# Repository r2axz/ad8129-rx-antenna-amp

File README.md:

# AD8129 RX Antenna Amp

This repository offers a KiCad project for DL2KQ high CMRR receiving antenna
amplifier. The amplifier is designed to work with magnetic loop, flag, ferrite
rod, and similar antennas. IIgor DL2KQ Goncharenko developed the original
circuit, which I left pretty much unchanged, except I added a couple of extra
capacitors for power supply and varactor bias decoupling. Refer to the original
post (in Russian) [http://dl2kq.de/ant/3-96.htm](http://dl2kq.de/ant/3-96.htm)
or [autogenerated English
translation](https://translate.google.com/translate?js=n&sl=auto&tl=en&u=http://dl2kq.de/ant/3-96.htm).

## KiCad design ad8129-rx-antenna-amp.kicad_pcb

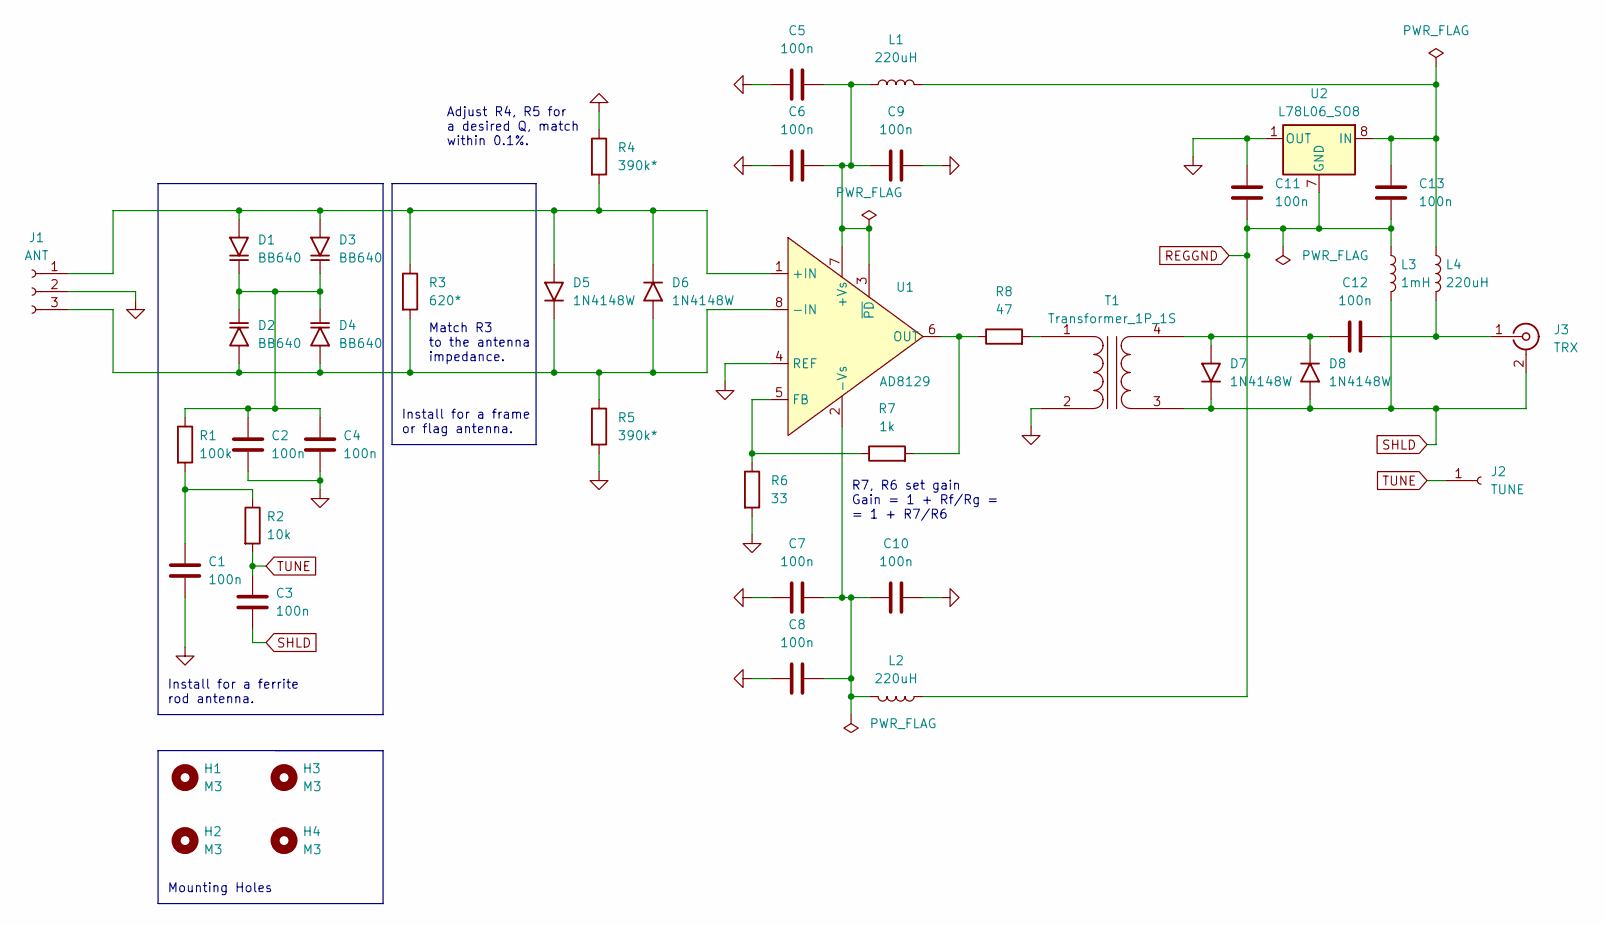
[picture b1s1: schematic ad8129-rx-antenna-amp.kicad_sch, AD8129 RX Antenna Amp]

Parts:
C1, C2, C3, C4, C5, C6, C7, C8, C9, C10, C11, C12, C13: 100n; C_0805_2012Metric
D1, D2, D3, D4: BB640; D_SOD-323
D5, D6, D7, D8: 1N4148W; D_SOD-123
H1, H2, H3, H4: M3; MountingHole_3.2mm_M3
J1: ANT; WirePad_3_0.8_1.5
J2: TUNE; WirePad_1_0.8_1.5
J3: TRX; SMA_Samtec_SMA-J-P-X-ST-EM1_EdgeMount
L1, L2, L4: 220uH; L_1812_4532Metric_Pad1.30x3.40mm_HandSolder
L3: 1mH; L_1812_4532Metric_Pad1.30x3.40mm_HandSolder
R1: 100k; R_0805_2012Metric
R2: 10k; R_0805_2012Metric
R3: 620*; R_0805_2012Metric
R4, R5: 390k*; R_0805_2012Metric
R6: 33; R_0805_2012Metric
R7: 1k; R_0805_2012Metric
R8: 47; R_0805_2012Metric
T1: Transformer_1P_1S; TR-FT-50-43-1P-1S-Isolated
U1: AD8129; SOIC-8_3.9x4.9mm_P1.27mm
U2: L78L06_SO8; SOIC-8_3.9x4.9mm_P1.27mm

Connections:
GND: C1.2, C2.2, C4.2, C5.1, C6.1, C7.2, C8.2, C9.2, C10.1, C11.1, J1.2, R4.1, R5.2, R6.2, T1.2 (AB), U1.4 (REF), U2.1 (OUT)
unnamed: C1.1, R1.2, R2.1
unnamed: C2.1, C4.1, D1.1 (K), D2.1 (K), D3.1 (K), D4.1 (K), R1.1
unnamed: C5.2, C6.2, C9.1, L1.1, U1.3 (~PD), U1.7 (+Vs)
unnamed: C7.1, C8.1, C10.2, L2.2, U1.2 (-Vs)
unnamed: C12.1, D7.2 (A), D8.1 (K), T1.4 (SB)
unnamed: C12.2, J3.1 (In), L4.2
unnamed: C13.1, L1.2, L4.1, U2.8 (IN)
unnamed: D1.2 (A), D3.2 (A), D5.2 (A), D6.1 (K), J1.1, R3.1, R4.2, U1.1 (+IN)
unnamed: D2.2 (A), D4.2 (A), D5.1 (K), D6.2 (A), J1.3, R3.2, R5.1, U1.8 (-IN)
unnamed: R6.1, R7.1, U1.5 (FB)
unnamed: R7.2, R8.1, U1.6 (OUT)
unnamed: R8.2, T1.1 (AA)
REGGND: C11.2, C13.2, L2.1, L3.1, U2.2 (GND), U2.3 (GND), U2.6 (GND), U2.7 (GND)
SHLD: C3.2, D7.1 (K), D8.2 (A), J3.2 (Ext), L3.2, T1.3 (SA)
TUNE: C3.1, J2.1, R2.2

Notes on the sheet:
Adjust R4, R5 for a desired Q, match within 0.1%.
Mounting Holes
R7, R6 set gain Gain = 1 + Rf/Rg = = 1 + R7/R6
Install for a ferrite rod antenna.
Match R3 to the antenna impedance.
Install for a frame or flag antenna.

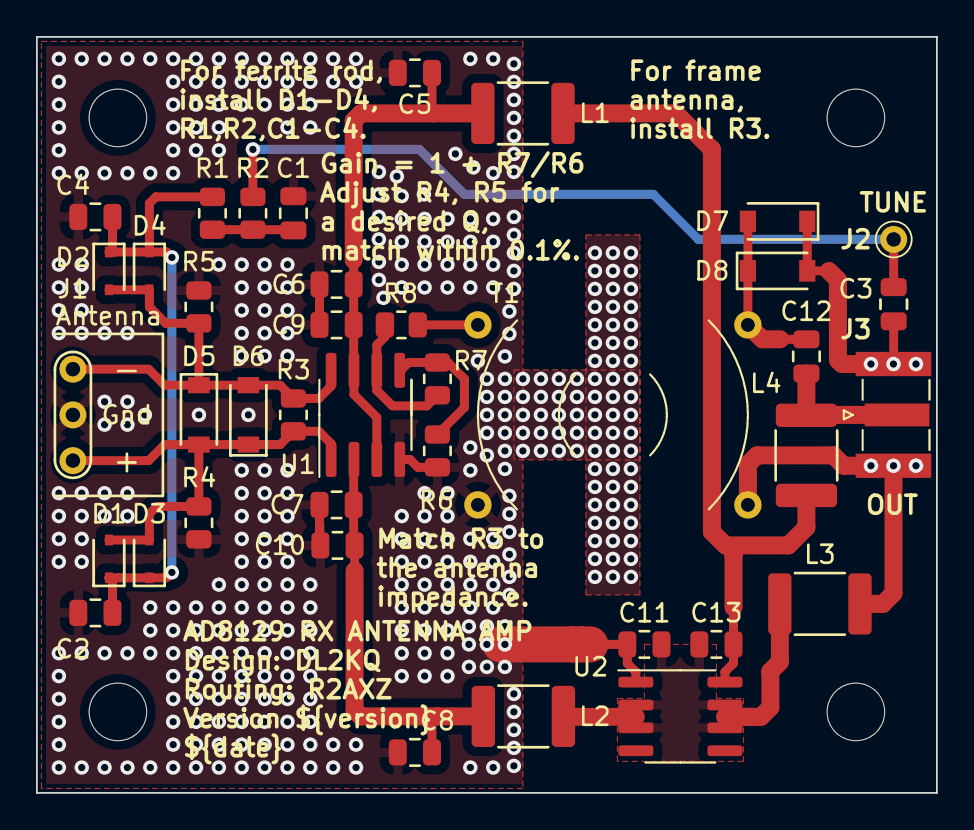
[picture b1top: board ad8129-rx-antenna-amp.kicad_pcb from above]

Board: 2 copper layers, 50.0 x 42.0 mm, 43 parts (0 on the bottom side), 16 nets.

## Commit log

2022-07-05 ADD: initial commit
2022-07-05 ADD: project symbol library
2022-07-05 ADD: standard symbols, varactor (wip)
2022-07-05 ADD: input stage
2022-07-05 ADD: preamp w/o varicap control
2022-07-05 ADD: tuning block, complete schematics, unverified
2022-07-05 FIX: frame
2022-07-05 FIX: U1 reference designator position
2022-07-05 ADD: footprint library
2022-07-05 ADD(WIP): board layout
2022-07-05 FIX: restore after crash
2022-07-05 FIX: pass ERC
2022-07-05 ADD: board name, revision, date. Board verified.
2022-07-05 FIX: remove the first take board
2022-07-06 FIX: remove test connector footprint
2022-07-06 FIX: silkscreen line width
2022-07-06 ADD: all footprints
2022-07-07 ADD: pcb layout, needs via stitching
2022-07-07 FIX: double check
2022-07-07 FIX: board position
2022-07-07 ADD: via stitching
2022-07-07 FIX: make burried vias, board info
2022-07-07 ADD: v1 final touch
2022-07-07 FIX: schematics name and date
2022-07-07 FIX: another final touch
2022-07-08 ADD: capacitors, T1 shield
2022-07-08 ADD: vias, fix DRC
2022-07-08 FIX: add vias
2022-07-08 FIX: final touches
2022-07-08 FIX: schematics layout
2022-07-08 ADD: kibot workflow
2022-07-08 ADD: kibot config
2022-07-08 FIX: paths
2022-07-08 FIX: use the right kibot config
2022-07-09 FIX: job tweaks
2022-07-09 FIX: output names
2022-07-09 FIX: board_black_bottom svg to png
2022-07-09 FIX: render tweaks
2022-07-09 FIX: increase render quality
2022-07-13 FIX: change project file names to match GitHub project name
2022-07-13 ADD: Sanity Check
2022-07-13 FIX: workflow file location
2022-07-13 FIX: pull-request --> pull_request
2022-07-13 FIX: trigger on files change
2022-07-13 FIX: sanity-check.yml location
2022-07-13 FIX: do not use spaces in job names
2022-07-13 FIX: kibot.yml --> .kibot.yml
2022-07-13 FIX: kibot call syntax
2022-07-13 ADD: give the job a name
2022-07-13 ADD: use separate jobs for ERC and DRC
2022-07-13 ADD: version and date variables
2022-07-13 FIX: variables case, board labels location
2022-07-13 ADD: basic project description
2022-07-13 FIX: title case
